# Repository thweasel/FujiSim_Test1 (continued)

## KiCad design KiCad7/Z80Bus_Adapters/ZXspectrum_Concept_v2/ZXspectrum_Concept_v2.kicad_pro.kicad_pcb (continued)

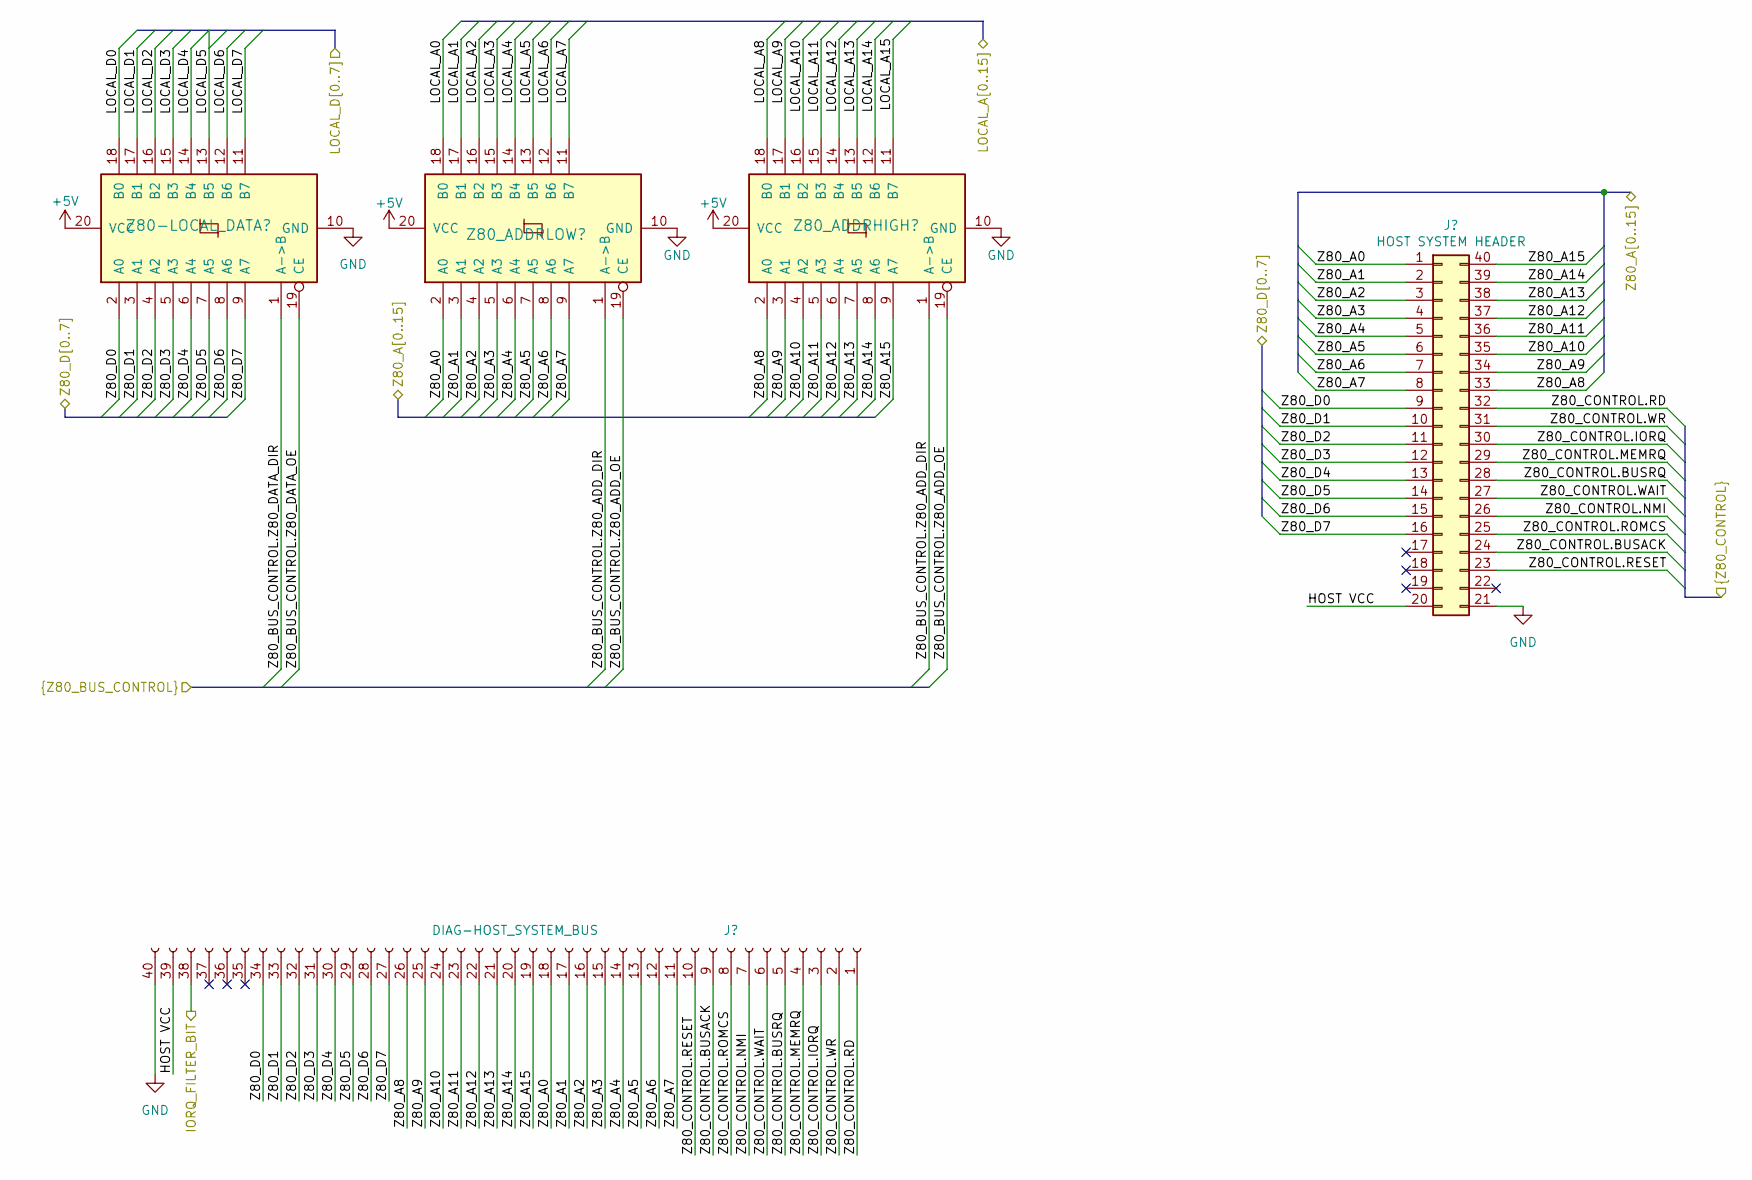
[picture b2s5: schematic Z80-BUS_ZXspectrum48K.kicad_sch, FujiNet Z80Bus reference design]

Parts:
J8: DIAG-HOST_SYSTEM_BUS; PinHeader_1x40_P2.54mm_Vertical
J9: HOST SYSTEM HEADER; PinHeader_2x20_P2.54mm_Vertical
Z80-LOCAL_DATA1, Z80_ADDRHIGH1, Z80_ADDRLOW1: 74HC245N; DIP-20_W7.62mm_Socket

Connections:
+5V: Z80-LOCAL_DATA1.20 (VCC), Z80_ADDRHIGH1.20 (VCC), Z80_ADDRLOW1.20 (VCC); also elsewhere on the board
/IORQ_FILTER_BITS: J8.38; also elsewhere on the board
/LOCAL_A0: Z80_ADDRLOW1.18 (B0); also elsewhere on the board
/LOCAL_A1: Z80_ADDRLOW1.17 (B1); also elsewhere on the board
/LOCAL_A2: Z80_ADDRLOW1.16 (B2); also elsewhere on the board
/LOCAL_A3: Z80_ADDRLOW1.15 (B3); also elsewhere on the board
/LOCAL_A4: Z80_ADDRLOW1.14 (B4); also elsewhere on the board
/LOCAL_A5: Z80_ADDRLOW1.13 (B5); also elsewhere on the board
/LOCAL_A6: Z80_ADDRLOW1.12 (B6); also elsewhere on the board
/LOCAL_A7: Z80_ADDRLOW1.11 (B7); also elsewhere on the board
/LOCAL_A8: Z80_ADDRHIGH1.18 (B0); also elsewhere on the board
/LOCAL_A9: Z80_ADDRHIGH1.17 (B1); also elsewhere on the board
/LOCAL_A10: Z80_ADDRHIGH1.16 (B2); also elsewhere on the board
/LOCAL_A11: Z80_ADDRHIGH1.15 (B3); also elsewhere on the board
/LOCAL_A12: Z80_ADDRHIGH1.14 (B4); also elsewhere on the board
/LOCAL_A13: Z80_ADDRHIGH1.13 (B5); also elsewhere on the board
/LOCAL_D0: Z80-LOCAL_DATA1.18 (B0); also elsewhere on the board
/LOCAL_D1: Z80-LOCAL_DATA1.17 (B1); also elsewhere on the board
/LOCAL_D2: Z80-LOCAL_DATA1.16 (B2); also elsewhere on the board
/LOCAL_D3: Z80-LOCAL_DATA1.15 (B3); also elsewhere on the board
/LOCAL_D4: Z80-LOCAL_DATA1.14 (B4); also elsewhere on the board
/LOCAL_D5: Z80-LOCAL_DATA1.13 (B5); also elsewhere on the board
/LOCAL_D6: Z80-LOCAL_DATA1.12 (B6); also elsewhere on the board
/LOCAL_D7: Z80-LOCAL_DATA1.11 (B7); also elsewhere on the board
/Z80_A0: J8.18, J9.1, Z80_ADDRLOW1.2 (A0); also elsewhere on the board
/Z80_A1: J8.17, J9.2, Z80_ADDRLOW1.3 (A1); also elsewhere on the board
/Z80_A2: J8.16, J9.3, Z80_ADDRLOW1.4 (A2); also elsewhere on the board
/Z80_A3: J8.15, J9.4, Z80_ADDRLOW1.5 (A3); also elsewhere on the board
/Z80_A4: J8.14, J9.5, Z80_ADDRLOW1.6 (A4); also elsewhere on the board
/Z80_A5: J8.13, J9.6, Z80_ADDRLOW1.7 (A5); also elsewhere on the board
/Z80_A6: J8.12, J9.7, Z80_ADDRLOW1.8 (A6); also elsewhere on the board
/Z80_A7: J8.11, J9.8, Z80_ADDRLOW1.9 (A7); also elsewhere on the board
/Z80_A8: J8.26, J9.33, Z80_ADDRHIGH1.2 (A0); also elsewhere on the board
/Z80_A9: J8.25, J9.34, Z80_ADDRHIGH1.3 (A1); also elsewhere on the board
/Z80_A10: J8.24, J9.35, Z80_ADDRHIGH1.4 (A2); also elsewhere on the board
/Z80_A11: J8.23, J9.36, Z80_ADDRHIGH1.5 (A3); also elsewhere on the board
/Z80_A12: J8.22, J9.37, Z80_ADDRHIGH1.6 (A4); also elsewhere on the board
/Z80_A13: J8.21, J9.38, Z80_ADDRHIGH1.7 (A5); also elsewhere on the board
/Z80_A14: J8.20, J9.39, Z80_ADDRHIGH1.8 (A6); also elsewhere on the board
/Z80_A15: J8.19, J9.40, Z80_ADDRHIGH1.9 (A7); also elsewhere on the board
/Z80_BUS_CONTROL.Z80_ADD_OE: Z80_ADDRHIGH1.19 (CE), Z80_ADDRLOW1.19 (CE); also elsewhere on the board
/Z80_BUS_CONTROL.Z80_DATA_DIR: Z80-LOCAL_DATA1.1 (A->B); also elsewhere on the board
/Z80_BUS_CONTROL.Z80_DATA_OE: Z80-LOCAL_DATA1.19 (CE); also elsewhere on the board
/Z80_CONTROL.BUSACK: J8.9, J9.24; also elsewhere on the board
/Z80_CONTROL.BUSRQ: J8.5, J9.28; also elsewhere on the board
/Z80_CONTROL.IORQ: J8.3, J9.30; also elsewhere on the board
/Z80_CONTROL.NMI: J8.7, J9.26; also elsewhere on the board
/Z80_CONTROL.RESET: J8.10, J9.23; also elsewhere on the board
/Z80_CONTROL.ROMCS: J8.8, J9.25; also elsewhere on the board
/Z80_CONTROL.WAIT: J8.6, J9.27; also elsewhere on the board
/Z80_CONTROL.WR: J8.2, J9.31; also elsewhere on the board
/Z80_D0: J8.34, J9.9, Z80-LOCAL_DATA1.2 (A0); also elsewhere on the board
/Z80_D1: J8.33, J9.10, Z80-LOCAL_DATA1.3 (A1); also elsewhere on the board
/Z80_D2: J8.32, J9.11, Z80-LOCAL_DATA1.4 (A2); also elsewhere on the board
/Z80_D3: J8.31, J9.12, Z80-LOCAL_DATA1.5 (A3); also elsewhere on the board
/Z80_D4: J8.30, J9.13, Z80-LOCAL_DATA1.6 (A4); also elsewhere on the board
/Z80_D5: J8.29, J9.14, Z80-LOCAL_DATA1.7 (A5); also elsewhere on the board
/Z80_D6: J8.28, J9.15, Z80-LOCAL_DATA1.8 (A6); also elsewhere on the board
/Z80_D7: J8.27, J9.16, Z80-LOCAL_DATA1.9 (A7); also elsewhere on the board
/ZX Spectrum Connector/HOST VCC: J8.39, J9.20

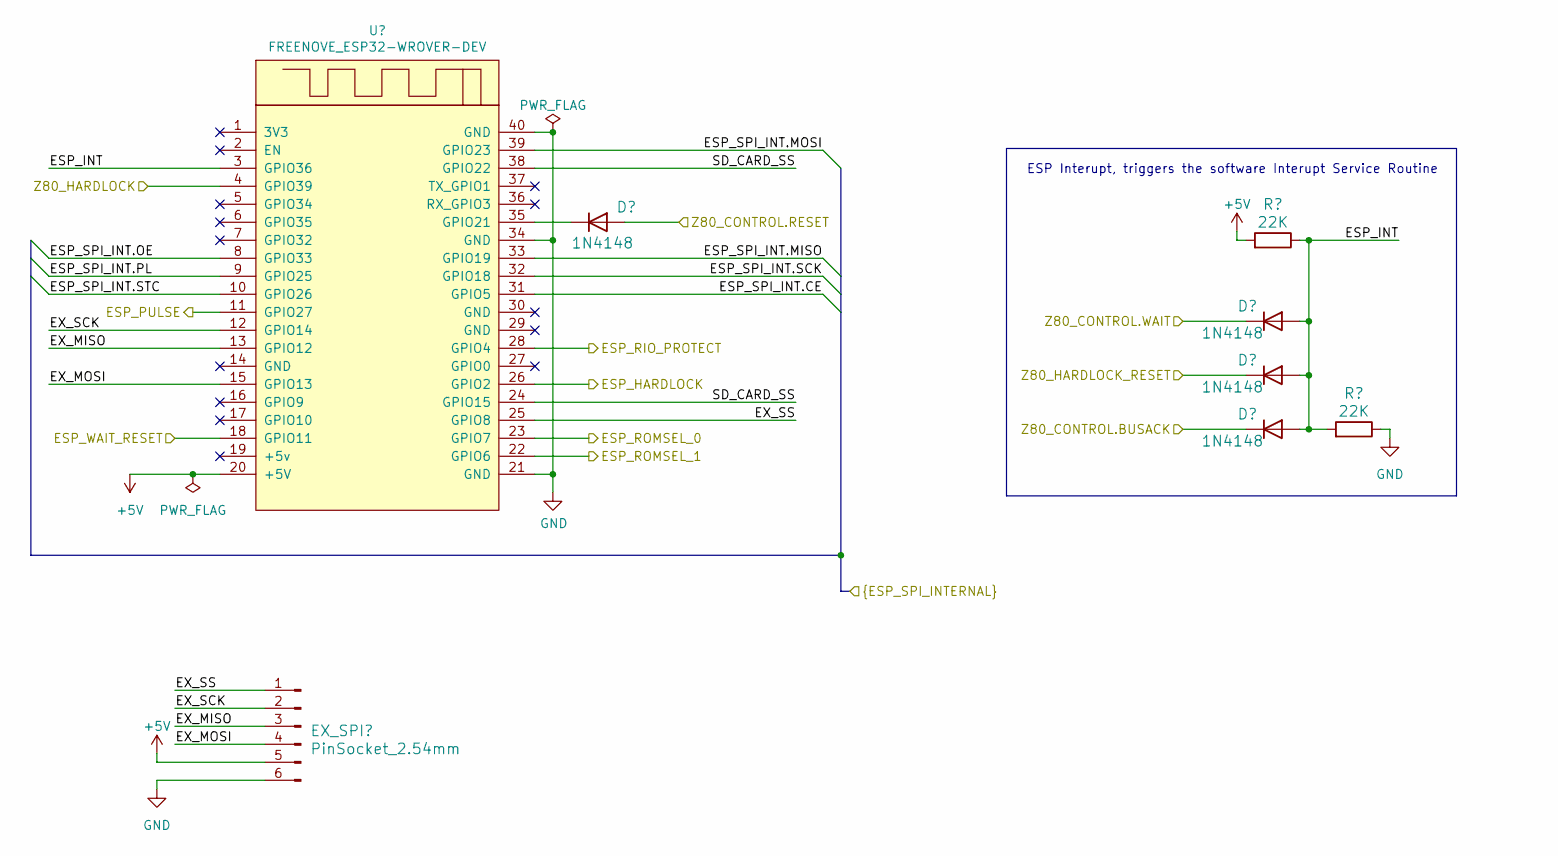
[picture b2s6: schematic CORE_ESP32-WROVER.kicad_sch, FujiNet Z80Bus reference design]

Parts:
D1, D2, D3, D4: 1N4148; D_T-1_P5.08mm_Horizontal
EX_SPI1: PinSocket_2.54mm; PinSocket_1x06_P2.54mm_Vertical
R1, R2: 22K; R_Axial_DIN0207_L6.3mm_D2.5mm_P10.16mm_Horizontal
U1: FREENOVE_ESP32-WROVER-DEV; Controller Daughter Board

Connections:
+5V: EX_SPI1.5, R1.2, U1.20 (+5V); also elsewhere on the board
/ESP32WRover/ESP_INT: D2.2 (A), D3.2 (A), D4.2 (A), R1.1, R2.2, U1.3 (GPIO36)
/ESP32WRover/EX_MISO: EX_SPI1.3, U1.13 (GPIO12)
/ESP32WRover/EX_MOSI: EX_SPI1.4, U1.15 (GPIO13)
/ESP32WRover/EX_SCK: EX_SPI1.2, U1.12 (GPIO14)
/ESP32WRover/EX_SS: EX_SPI1.1, U1.25 (GPIO8)
/ESP32WRover/SD_CARD_SS: U1.24 (GPIO15), U1.38 (GPIO22)
/ESP PULSE: U1.11 (GPIO27); also elsewhere on the board
/ESP_HARDLOCK: U1.26 (GPIO2); also elsewhere on the board
/ESP_ROMSEL_0: U1.23 (GPIO7); also elsewhere on the board
/ESP_ROMSEL_1: U1.22 (GPIO6); also elsewhere on the board
/ESP_SPI_INT.CE: U1.31 (GPIO5); also elsewhere on the board
/ESP_SPI_INT.MISO: U1.33 (GPIO19); also elsewhere on the board
/ESP_SPI_INT.MOSI: U1.39 (GPIO23); also elsewhere on the board
/ESP_SPI_INT.OE: U1.8 (GPIO33); also elsewhere on the board
/ESP_SPI_INT.PL: U1.9 (GPIO25); also elsewhere on the board
/ESP_SPI_INT.SCK: U1.32 (GPIO18); also elsewhere on the board
/ESP_SPI_INT.STC: U1.10 (GPIO26); also elsewhere on the board
/ESP_WAIT_RESET: U1.18 (GPIO11); also elsewhere on the board
/Z80_CONTROL.BUSACK: D4.1 (K); also elsewhere on the board
/Z80_CONTROL.RESET: D1.2 (A); also elsewhere on the board
/Z80_CONTROL.WAIT: D2.1 (K); also elsewhere on the board
/Z80_HARDLOCK: U1.4 (GPIO39); also elsewhere on the board
/Z80_HARDLOCK_RESET: D3.1 (K); also elsewhere on the board
unnamed: D1.1 (K), U1.35 (GPIO21)

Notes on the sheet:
ESP Interupt, triggers the software Interupt Service Routine

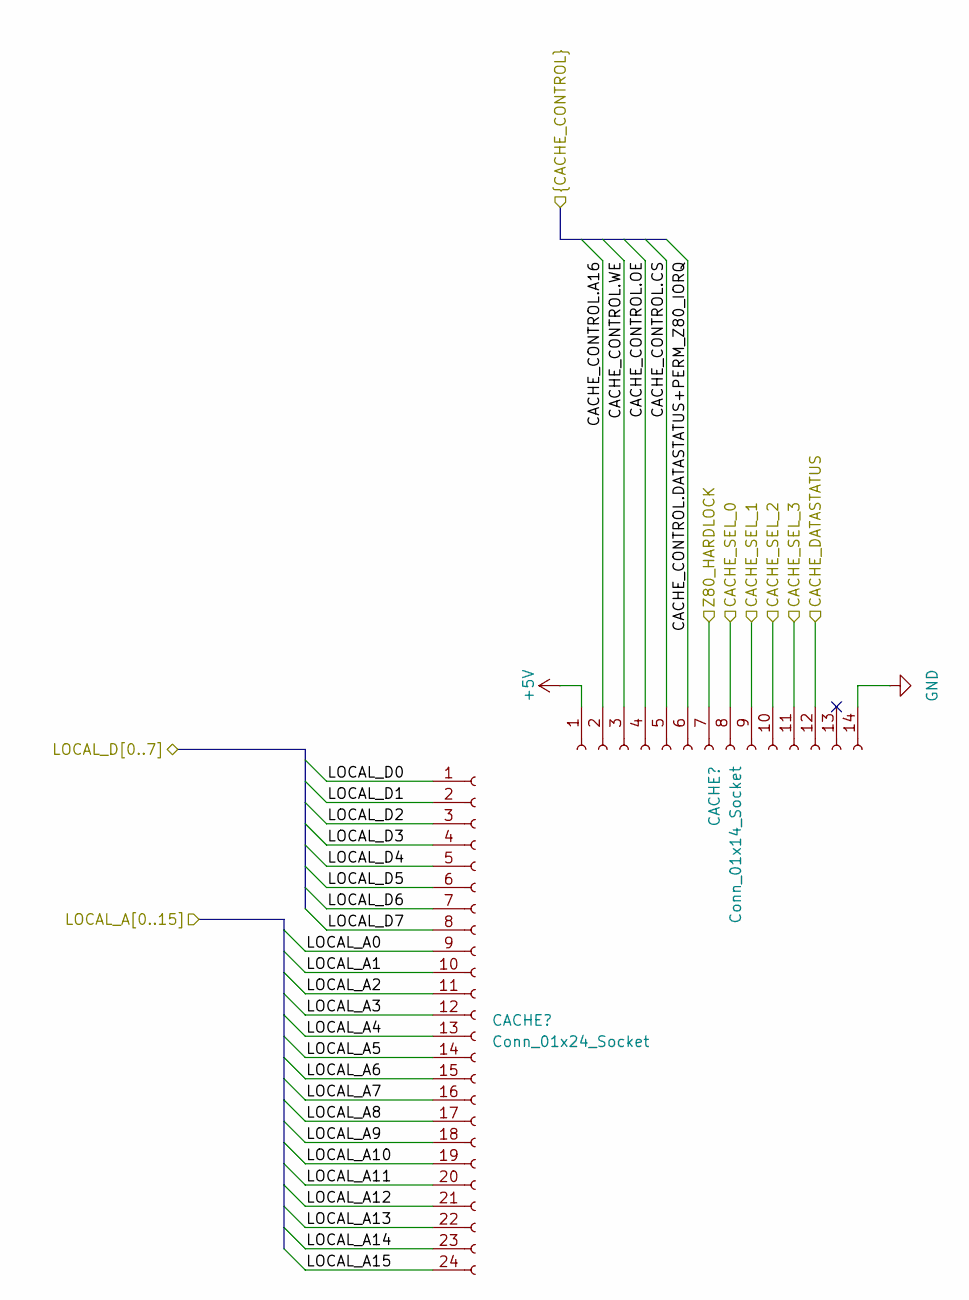
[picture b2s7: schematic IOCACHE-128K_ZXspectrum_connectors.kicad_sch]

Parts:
CACHE1: Conn_01x24_Socket; PinSocket_1x24_P2.54mm_Vertical
CACHE2: Conn_01x14_Socket; PinSocket_1x14_P2.54mm_Vertical

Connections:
+5V: CACHE2.1; also elsewhere on the board
/CACHE_CONTROL.A16: CACHE2.2; also elsewhere on the board
/CACHE_CONTROL.CS: CACHE2.5; also elsewhere on the board
/CACHE_CONTROL.DATASTATUS+PERM_Z80_IORQ: CACHE2.6; also elsewhere on the board
/CACHE_CONTROL.OE: CACHE2.4; also elsewhere on the board
/CACHE_CONTROL.WE: CACHE2.3; also elsewhere on the board
/CACHE_SEL_0: CACHE2.8; also elsewhere on the board
/CACHE_SEL_1: CACHE2.9; also elsewhere on the board
/CACHE_SEL_2: CACHE2.10; also elsewhere on the board
/CACHE_SEL_3: CACHE2.11; also elsewhere on the board
/LOCAL_A0: CACHE1.9; also elsewhere on the board
/LOCAL_A1: CACHE1.10; also elsewhere on the board
/LOCAL_A2: CACHE1.11; also elsewhere on the board
/LOCAL_A3: CACHE1.12; also elsewhere on the board
/LOCAL_A4: CACHE1.13; also elsewhere on the board
/LOCAL_A5: CACHE1.14; also elsewhere on the board
/LOCAL_A6: CACHE1.15; also elsewhere on the board
/LOCAL_A7: CACHE1.16; also elsewhere on the board
/LOCAL_A8: CACHE1.17; also elsewhere on the board
/LOCAL_A9: CACHE1.18; also elsewhere on the board
/LOCAL_A10: CACHE1.19; also elsewhere on the board
/LOCAL_A11: CACHE1.20; also elsewhere on the board
/LOCAL_A12: CACHE1.21; also elsewhere on the board
/LOCAL_A13: CACHE1.22; also elsewhere on the board
/LOCAL_D0: CACHE1.1; also elsewhere on the board
/LOCAL_D1: CACHE1.2; also elsewhere on the board
/LOCAL_D2: CACHE1.3; also elsewhere on the board
/LOCAL_D3: CACHE1.4; also elsewhere on the board
/LOCAL_D4: CACHE1.5; also elsewhere on the board
/LOCAL_D5: CACHE1.6; also elsewhere on the board
/LOCAL_D6: CACHE1.7; also elsewhere on the board
/LOCAL_D7: CACHE1.8; also elsewhere on the board
/Z80_HARDLOCK: CACHE2.7; also elsewhere on the board

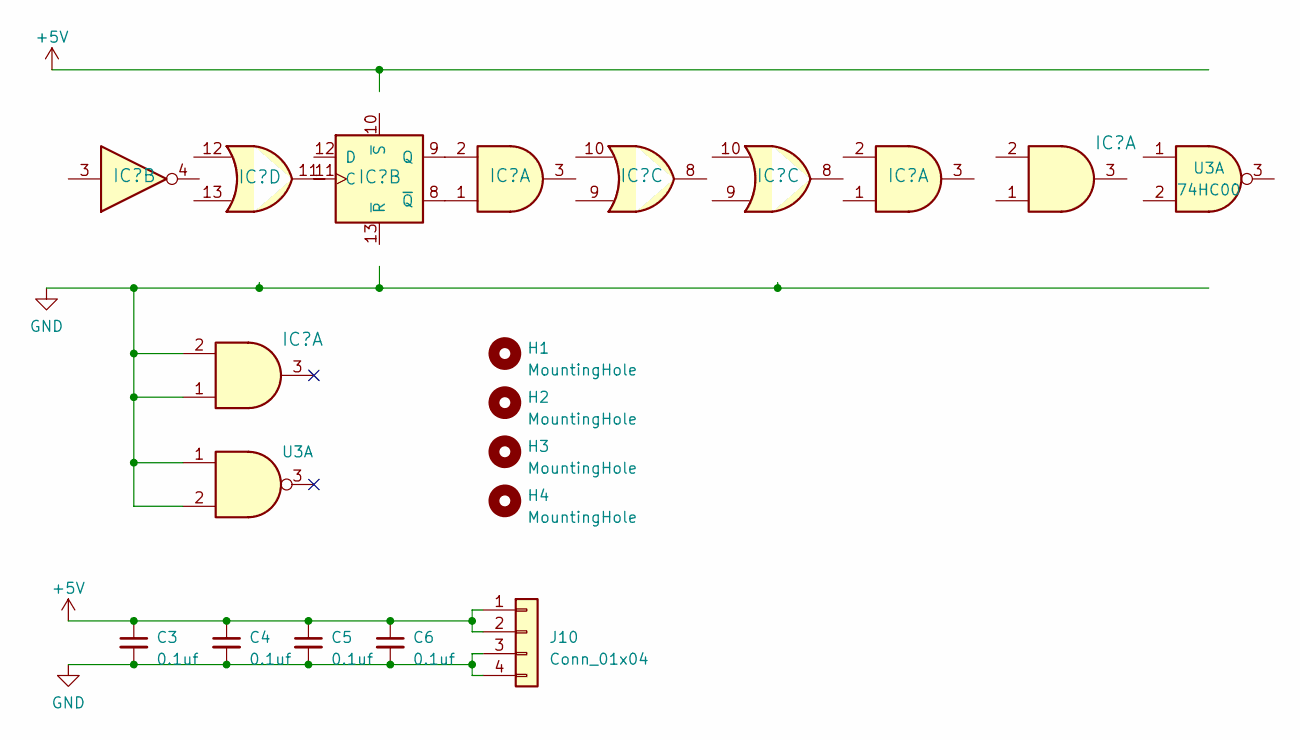
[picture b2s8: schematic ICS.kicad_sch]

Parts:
C3, C4, C5, C6: 0.1uf; C_Disc_D7.5mm_W2.5mm_P5.00mm
H1, H2, H3, H4: MountingHole; MountingHole_2.2mm_M2
IC1: 7404N; DIP-14_W7.62mm_Socket
IC2, IC5, IC6: 74HC32N; DIP-14_W7.62mm_Socket
IC3: 7474N; DIP-14_W7.62mm_Socket
IC4, IC8, IC9: 74HC08N; DIP-14_W7.62mm_Socket
J10: Conn_01x04; PinHeader_1x04_P2.54mm_Vertical
U3: 74HC00; DIP-14_W7.62mm

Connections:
+5V: C3.1, C4.1, C5.1, C6.1, IC3.14 (VCC), J10.1, J10.2; also elsewhere on the board
/CACHE_CONTROL.A16: IC6.11; also elsewhere on the board
/ESP_CONTROL.ROMCS: IC1.13, IC5.5; also elsewhere on the board
/ESP_CONTROL.WR: IC6.9; also elsewhere on the board
/ESP_WAIT_RESET: IC3.13 (~R); also elsewhere on the board
/Glue Logic/CLR_Z80_HARDLOCK: IC4.3; also elsewhere on the board
/Glue Logic/PRE_Z80_HARDLOCK: IC1.4; also elsewhere on the board
/IORQ_FILTER_BITS: IC2.12; also elsewhere on the board
/LOCAL_CONTROL.IORQ: IC6.13; also elsewhere on the board
/RIO_CONTROL.A14: U3.3 (2Y0); also elsewhere on the board
/RIO_CONTROL.CE: IC8.6; also elsewhere on the board
/Z80_BUS_CONTROL.Z80_ADD_OE: IC8.8; also elsewhere on the board
/Z80_BUS_CONTROL.Z80_DATA_DIR: IC6.8; also elsewhere on the board
/Z80_CONTROL.ROMCS: IC1.12; also elsewhere on the board
/Z80_HARDLOCK_SET: IC1.3; also elsewhere on the board
unnamed 116: IC2.13; also elsewhere on the board
unnamed 117: IC3.10 (~S); also elsewhere on the board
unnamed 119: IC6.10; also elsewhere on the board

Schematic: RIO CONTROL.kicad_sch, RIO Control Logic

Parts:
D6: 1N4148; D_T-1_P5.08mm_Horizontal
IC4, IC6, IC8: 74HC08N; DIP-14_W7.62mm_Socket
IC5, IC7: 74HC32N; DIP-14_W7.62mm_Socket
RN1: 4609M-101-103LF; R_Array_SIP9
U2: 74HC00; DIP-14_W7.62mm
U3: 74HC244N; DIP-20_W7.62mm_Socket

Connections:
+5V: D6.2 (A), U2.14 (VCC), U3.20 (VCC); also elsewhere on the board
/CACHE_CONTROL.A16: IC6.11; also elsewhere on the board
/ESP_CONTROL.BUSRQ: IC7.4; also elsewhere on the board
/ESP_CONTROL.IORQ: IC4.5; also elsewhere on the board
/ESP_CONTROL.MEMRQ: IC4.4; also elsewhere on the board
/ESP_CONTROL.ROMCS: IC5.5; also elsewhere on the board
/ESP_ROMSEL_0: U3.15 (2A1); also elsewhere on the board
/ESP_ROMSEL_1: U3.17 (2A0); also elsewhere on the board
/Glue Logic/RIO CONTROL/PERMITTED_RIO_WR: IC5.11, U3.6 (1A2), U3.13 (2A2)
/LOCAL_CONTROL.IORQ: IC6.13; also elsewhere on the board
/RIO_CONTROL.A14: RN1.2 (R1), U3.3 (2Y0), U3.18 (1Y0); also elsewhere on the board
/RIO_CONTROL.A15: RN1.3 (R2), U3.5 (2Y1), U3.16 (1Y1); also elsewhere on the board
/RIO_CONTROL.CE: IC8.6; also elsewhere on the board
/RIO_CONTROL.OE: RN1.5 (R4), U3.9 (2Y3), U3.12 (1Y3); also elsewhere on the board
/RIO_CONTROL.WE: RN1.4 (R3), U3.7 (2Y2), U3.14 (1Y2); also elsewhere on the board
/Z80_BUS_CONTROL.Z80_ADD_OE: IC8.8; also elsewhere on the board
/Z80_BUS_CONTROL.Z80_DATA_OE: IC7.11; also elsewhere on the board
/Z80_CONTROL.WR: IC5.12; also elsewhere on the board
unnamed: D6.1 (K), RN1.1 (common)
unnamed: IC4.6, U2.1, U2.2
unnamed: U2.3, U2.4
unnamed: U2.6, U2.9, U2.10

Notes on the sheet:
There is room to improve on this decoding circuit
Host ROM base address
RIO Access conditions
ESP programming IOD
RIO write protection
RIO IOD ACCESS
RIO ROM ACCESS

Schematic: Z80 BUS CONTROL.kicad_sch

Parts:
IC1: 7404N; DIP-14_W7.62mm_Socket
IC2, IC5, IC7: 74HC32N; DIP-14_W7.62mm_Socket
IC6, IC8: 74HC08N; DIP-14_W7.62mm_Socket

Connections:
/CACHE_CONTROL.A16: IC6.11; also elsewhere on the board
/ESP_CONTROL.BUSRQ: IC2.1, IC7.4; also elsewhere on the board
/ESP_CONTROL.ROMCS: IC1.13, IC5.5; also elsewhere on the board
/ESP_CONTROL.WR: IC6.9; also elsewhere on the board
/ESP_HARDLOCK: IC1.1; also elsewhere on the board
/LOCAL_CONTROL.IORQ: IC6.13; also elsewhere on the board
/RIO_CONTROL.CE: IC8.6; also elsewhere on the board
/Z80_BUS_CONTROL.Z80_ADD_OE: IC8.8; also elsewhere on the board
/Z80_BUS_CONTROL.Z80_DATA_DIR: IC6.8; also elsewhere on the board
/Z80_BUS_CONTROL.Z80_DATA_OE: IC7.11; also elsewhere on the board
/Z80_CONTROL.BUSACK: IC2.2; also elsewhere on the board
/Z80_CONTROL.ROMCS: IC1.12; also elsewhere on the board
unnamed: IC6.10, IC7.3

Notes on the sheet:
ESP driving the host system
Z80 IO Request to Status (single Byte) registers

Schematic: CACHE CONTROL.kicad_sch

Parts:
IC2: 74HC32N; DIP-14_W7.62mm_Socket
IC4, IC6: 74HC08N; DIP-14_W7.62mm_Socket

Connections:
/CACHE_CONTROL.A16: IC6.11; also elsewhere on the board
/CACHE_CONTROL.CS: IC4.11; also elsewhere on the board
/CACHE_CONTROL.DATASTATUS+PERM_Z80_IORQ: IC2.6; also elsewhere on the board
/CACHE_CONTROL.OE: IC4.8; also elsewhere on the board
/CACHE_CONTROL.WE: IC6.6; also elsewhere on the board
/LOCAL_CONTROL.IORQ: IC6.13; also elsewhere on the board
/LOCAL_CONTROL.MEMRQ: IC4.13; also elsewhere on the board
/LOCAL_CONTROL.RD: IC4.10; also elsewhere on the board
/LOCAL_CONTROL.WR: IC6.5; also elsewhere on the board
/PERM_Z80_IORQ: IC2.4, IC4.12; also elsewhere on the board
/Z80_CONTROL.WR: IC6.4; also elsewhere on the board

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
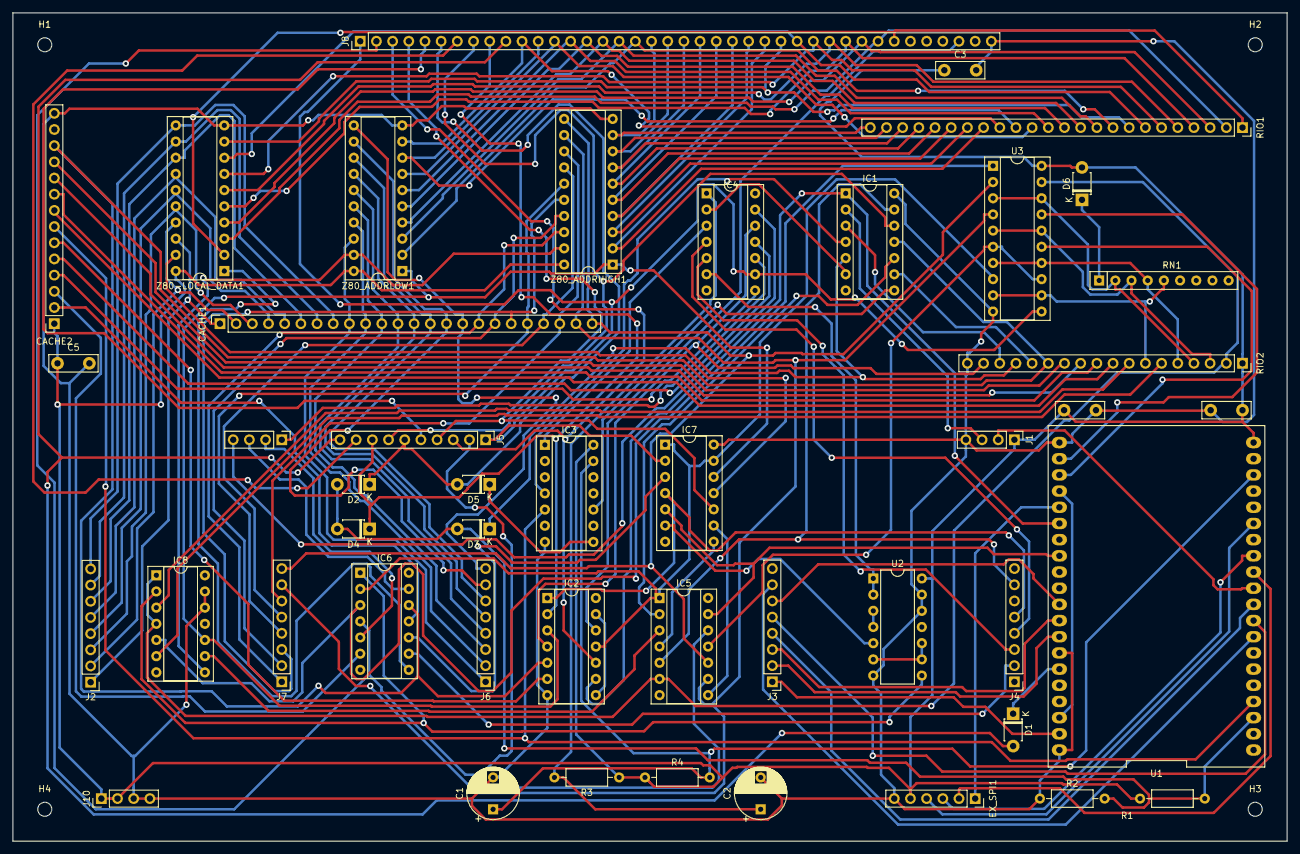
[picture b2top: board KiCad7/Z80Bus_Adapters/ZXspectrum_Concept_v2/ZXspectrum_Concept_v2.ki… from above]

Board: 2 copper layers, 200.0 x 130.0 mm, 50 parts (0 on the bottom side), 138 nets.
